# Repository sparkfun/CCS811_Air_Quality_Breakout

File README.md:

SparkFun CCS811 Air Quality Breakout
========================================

[*SparkFun CCS811 (SEN-14193)*](https://www.sparkfun.com/products/14193)

The CCS811 is an digital gas sensor solution which integrates a metal oxide (MOX) gas sensor to detect a wide range of Volatile Organic Compounds (VOCs) for indoor air quality monitoring.

This product is designed to provide an easy hardware and software interface to the CCS811 sensor.

Repository Contents
-------------------

* **/Documentation** - Data sheets, additional product information
* **/Hardware** - Eagle design files (.brd, .sch)
* **/Production** - Production panel files (.brd)
* **/Software** - Python scripts for CCS811

Documentation
--------------
* **[Library](https://github.com/sparkfun/SparkFun_CCS811_Arduino_Library)** - Arduino library for the CCS811.
* **[Hookup Guide](https://learn.sparkfun.com/tutorials/ccs811-air-quality-breakout-hookup-guide)** - Basic hookup guide for the CCS811.
* **[SparkFun Fritzing repo](https://github.com/sparkfun/Fritzing_Parts)** - Fritzing diagrams for SparkFun products.
* **[SparkFun 3D Model repo](https://github.com/sparkfun/3D_Models)** - 3D models of SparkFun products. 

Product Versions
----------------
* [SEN-14193](https://www.sparkfun.com/)- CCS811 Breakout board

Version History
---------------
* [V 1.0.0](https://github.com/sparkfun/CCS811_Air_Quality_Breakout/tree/V_1.0.0) -- Initial commit of Arduino compatible library.

License Information
-------------------

This product is _**open source**_! 

Please review the LICENSE.md file for license information. 

If you have any questions or concerns on licensing, please contact techsupport@sparkfun.com.

Distributed as-is; no warranty is given.

- Your friends at SparkFun.

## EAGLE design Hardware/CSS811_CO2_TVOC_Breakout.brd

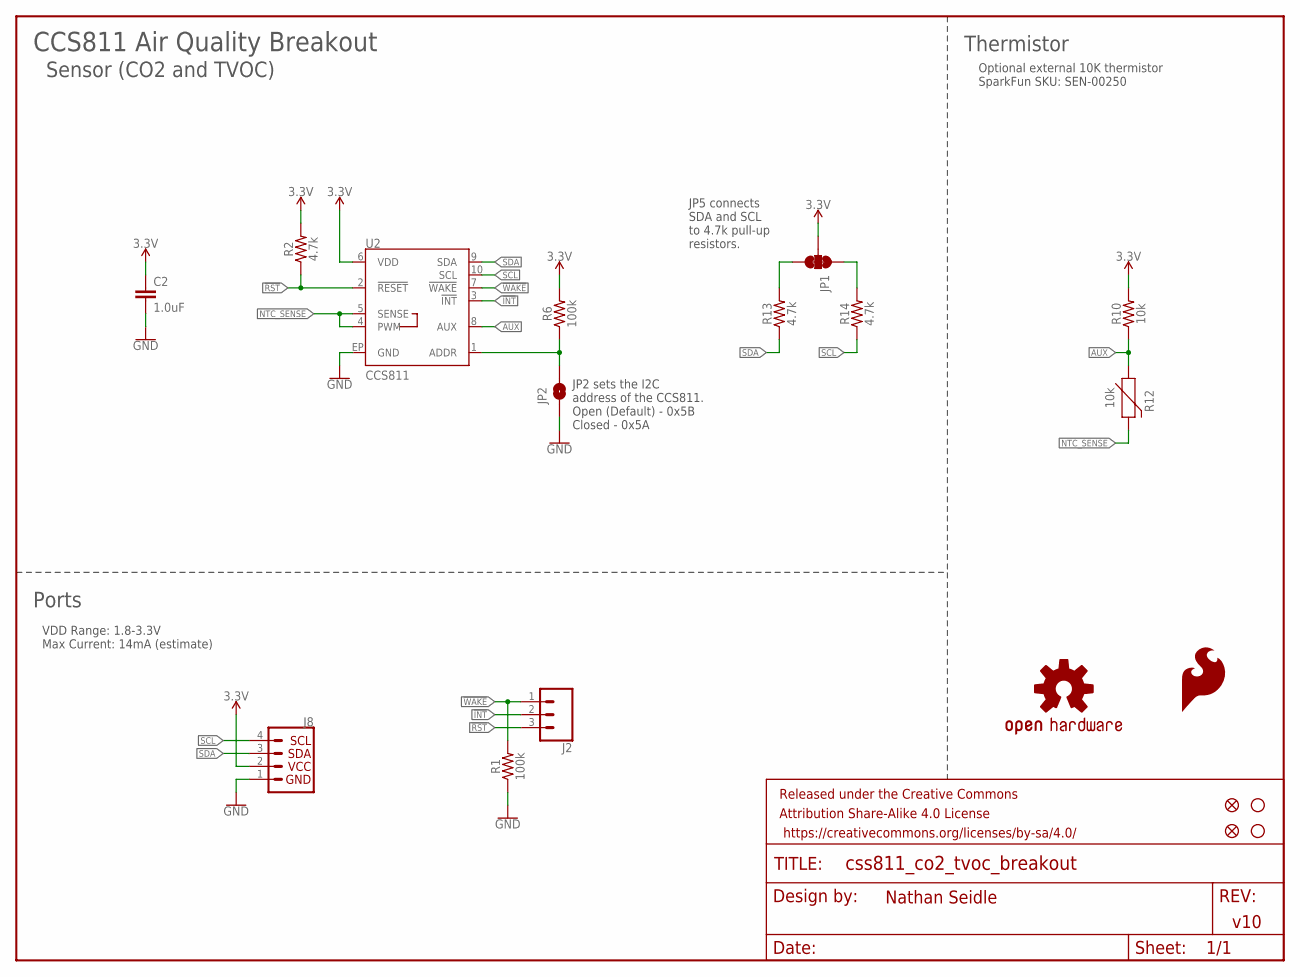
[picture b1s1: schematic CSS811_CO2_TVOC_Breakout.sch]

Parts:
C2: 1.0uF; 0603
FD1, FD2: FIDUCIAL1X2; FIDUCIAL-1X2
FRAME1: FRAME-LETTER; CREATIVE_COMMONS
H2, H4: STAND-OFF
J2: CONN_031X03_NO_SILK; 1X03_NO_SILK
J8: I2C_STANDARD_NO_SILK; 1X04_NO_SILK
JP1: JUMPER-SMT_3_2-NC_TRACE_SILK; SMT-JUMPER_3_2-NC_TRACE_SILK
JP2: JUMPER-SMT_2_NO_SILK; SMT-JUMPER_2_NO_SILK
LOGO1: SFE_LOGO_FLAME.2_INCH; SFE_LOGO_FLAME_.2
LOGO4: OSHW-LOGOS; OSHW-LOGO-S
R1, R6: 100k; 0603
R2, R13, R14: 4.7k; 0603
R10: 10k; 0603
R12: 10k; AXIAL-0.1
U2: CCS811; LGA10

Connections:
3.3V: C2.1, J8.2, JP1.2, R2.2, R6.2, R10.2, U2.6 (VDD)
!INT: J2.2, U2.3 (!INT!)
!RST: J2.3, R2.1, U2.2 (!RESET!)
!WAKE: J2.1, R1.2, U2.7 (!WAKE!)
AUX: R10.1, R12.P$1 (1), U2.8 (AUX)
CCS811_ADDR: JP2.2, R6.1, U2.1 (ADDR)
GND: C2.2, J8.1, JP2.1, R1.1, U2.EP (GND)
unnamed: JP1.3, R13.2
unnamed: JP1.1, R14.2
NTC_SENSE: R12.P$2 (2), U2.4 (PWM), U2.5 (SENSE)
SCL: J8.4, R14.1, U2.10 (SCL)
SDA: J8.3, R13.1, U2.9 (SDA)

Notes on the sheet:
VDD Range: 1.8-3.3V Max Current: 14mA (estimate)
CCS811 Air Quality Breakout
JP2 sets the I2C address of the CCS811. Open (Default) - 0x5B Closed - 0x5A
JP5 connects SDA and SCL to 4.7k pull-up resistors.
v10
Nathan Seidle
Optional external 10K thermistor SparkFun SKU: SEN-00250
Ports
Thermistor
Sensor (CO2 and TVOC)

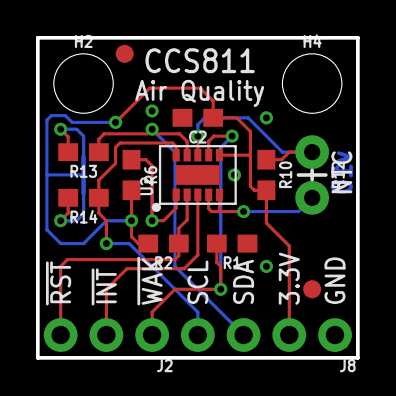
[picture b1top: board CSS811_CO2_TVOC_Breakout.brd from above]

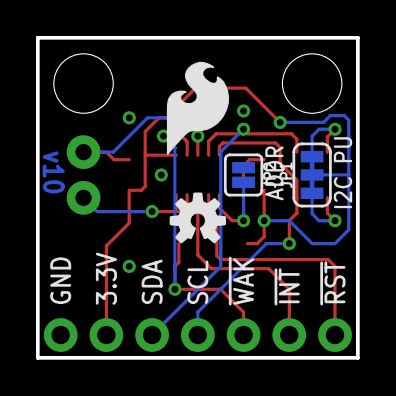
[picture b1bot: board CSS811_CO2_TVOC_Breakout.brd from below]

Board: 2 copper layers, 17.8 x 17.8 mm, 20 parts (4 on the bottom side), 12 nets.

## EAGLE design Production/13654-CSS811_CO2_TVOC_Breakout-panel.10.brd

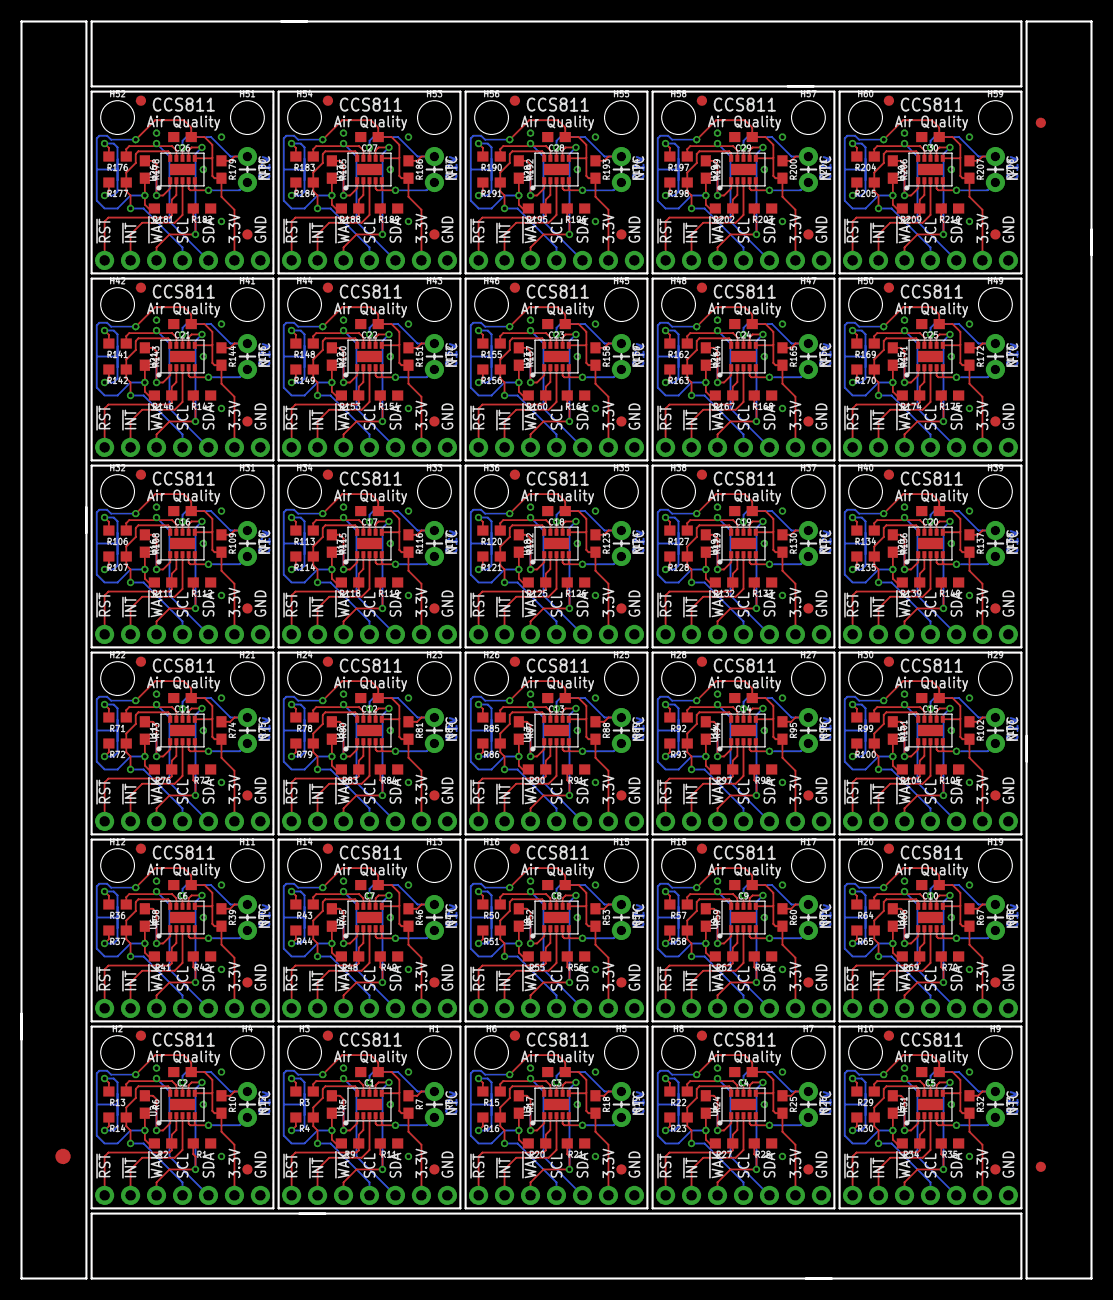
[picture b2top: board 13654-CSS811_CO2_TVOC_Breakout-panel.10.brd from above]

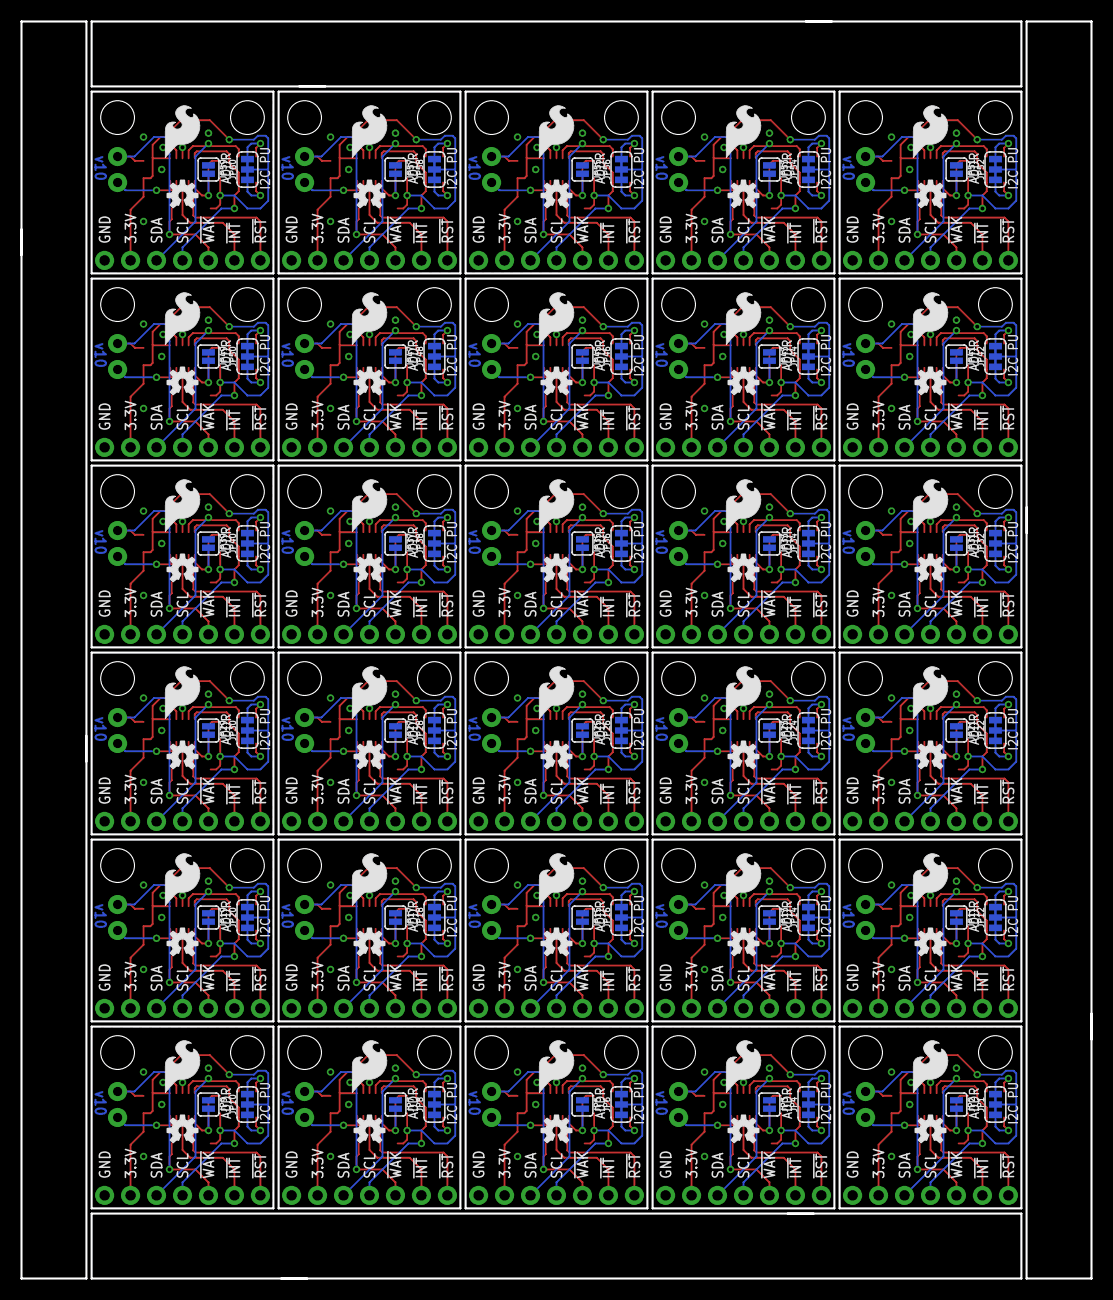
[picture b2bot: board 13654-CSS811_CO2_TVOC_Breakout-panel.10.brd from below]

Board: 2 copper layers, 104.6 x 122.9 mm, 573 parts (120 on the bottom side), 360 nets.

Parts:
C1, C2, C3, C4, C5, C6, C7, C8, C9, C10, C11, C12, C13, C14, C15, C16, C17, C18, C19, C20, C21, C22, C23, C24, C25, C26, C27, C28, C29, C30: 1.0uF; 0603
E$1: FIDUCIAL-1.5X3
E$7, E$8: FIDUCIAL-1X2
FD1, FD2, FD3, FD4, FD5, FD6, FD7, FD8, FD9, FD10, FD11, FD12, FD13, FD14, FD15, FD16, FD17, FD18, FD19, FD20, FD21, FD22, FD23, FD24, FD25, FD26, FD27, FD28, FD29, FD30, FD31, FD32, FD33, FD34, FD35, FD36, FD37, FD38, FD39, FD40, FD41, FD42, FD43, FD44, FD45, FD46, FD47, FD48, FD49, FD50, FD51, FD52, FD53, FD54, FD55, FD56, FD57, FD58, FD59, FD60: FIDUCIAL1X2; FIDUCIAL-1X2
H1, H2, H3, H4, H5, H6, H7, H8, H9, H10, H11, H12, H13, H14, H15, H16, H17, H18, H19, H20, H21, H22, H23, H24, H25, H26, H27, H28, H29, H30, H31, H32, H33, H34, H35, H36, H37, H38, H39, H40, H41, H42, H43, H44, H45, H46, H47, H48, H49, H50, H51, H52, H53, H54, H55, H56, H57, H58, H59, H60: STAND-OFF
J1, J4, J6, J8, J9, J11, J13, J15, J17, J19, J21, J23, J25, J27, J29, J31, J33, J35, J37, J39, J41, J43, J45, J47, J49, J51, J53, J55, J57, J59: 1X04_NO_SILK
J2, J3, J5, J7, J10, J12, J14, J16, J18, J20, J22, J24, J26, J28, J30, J32, J34, J36, J38, J40, J42, J44, J46, J48, J50, J52, J54, J56, J58, J60: 1X03_NO_SILK
JP1, JP4, JP6, JP8, JP10, JP12, JP14, JP16, JP18, JP20, JP22, JP24, JP26, JP28, JP30, JP32, JP34, JP36, JP38, JP40, JP42, JP44, JP46, JP48, JP50, JP52, JP54, JP56, JP58, JP60: SMT-JUMPER_3_2-NC_TRACE_SILK
JP2, JP3, JP5, JP7, JP9, JP11, JP13, JP15, JP17, JP19, JP21, JP23, JP25, JP27, JP29, JP31, JP33, JP35, JP37, JP39, JP41, JP43, JP45, JP47, JP49, JP51, JP53, JP55, JP57, JP59: SMT-JUMPER_2_NO_SILK
LOGO1, LOGO3, LOGO6, LOGO8, LOGO10, LOGO12, LOGO14, LOGO16, LOGO18, LOGO20, LOGO22, LOGO24, LOGO26, LOGO28, LOGO30, LOGO32, LOGO34, LOGO36, LOGO38, LOGO40, LOGO42, LOGO44, LOGO46, LOGO48, LOGO50, LOGO52, LOGO54, LOGO56, LOGO58, LOGO60: SFE_LOGO_FLAME.2_INCH; SFE_LOGO_FLAME_.2
LOGO2, LOGO4, LOGO5, LOGO7, LOGO9, LOGO11, LOGO13, LOGO15, LOGO17, LOGO19, LOGO21, LOGO23, LOGO25, LOGO27, LOGO29, LOGO31, LOGO33, LOGO35, LOGO37, LOGO39, LOGO41, LOGO43, LOGO45, LOGO47, LOGO49, LOGO51, LOGO53, LOGO55, LOGO57, LOGO59: OSHW-LOGOS; OSHW-LOGO-S
R1, R5, R6, R11, R17, R21, R24, R28, R31, R35, R38, R42, R45, R49, R52, R56, R59, R63, R66, R70, R73, R77, R80, R84, R87, R91, R94, R98, R101, R105, R108, R112, R115, R119, R122, R126, R129, R133, R136, R140, R143, R147, R150, R154, R157, R161, R164, R168, R171, R175, R178, R182, R185, R189, R192, R196, R199, R203, R206, R210: 100k; 0603
R2, R3, R4, R9, R13, R14, R15, R16, R20, R22, R23, R27, R29, R30, R34, R36, R37, R41, R43, R44, R48, R50, R51, R55, R57, R58, R62, R64, R65, R69, R71, R72, R76, R78, R79, R83, R85, R86, R90, R92, R93, R97, R99, R100, R104, R106, R107, R111, R113, R114, R118, R120, R121, R125, R127, R128, R132, R134, R135, R139, R141, R142, R146, R148, R149, R153, R155, R156, R160, R162, R163, R167, R169, R170, R174, R176, R177, R181, R183, R184, R188, R190, R191, R195, R197, R198, R202, R204, R205, R209: 4.7k; 0603
R7, R10, R18, R25, R32, R39, R46, R53, R60, R67, R74, R81, R88, R95, R102, R109, R116, R123, R130, R137, R144, R151, R158, R165, R172, R179, R186, R193, R200, R207: 10k; 0603
R8, R12, R19, R26, R33, R40, R47, R54, R61, R68, R75, R82, R89, R96, R103, R110, R117, R124, R131, R138, R145, R152, R159, R166, R173, R180, R187, R194, R201, R208: 10k; AXIAL-0.1
U1, U2, U3, U4, U5, U6, U7, U8, U9, U10, U11, U12, U13, U14, U15, U16, U17, U18, U19, U20, U21, U22, U23, U24, U25, U26, U27, U28, U29, U30: CCS811; LGA10

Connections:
3.3V: C2.1, J8.2, JP1.2, R2.2, R6.2, R10.2, U2.6
3.3V1: C1.1, J1.2, JP4.2, R5.2, R7.2, R9.2, U1.6
3.3V2: C3.1, J4.2, JP6.2, R17.2, R18.2, R20.2, U3.6
3.3V3: C4.1, J6.2, JP8.2, R24.2, R25.2, R27.2, U4.6
3.3V4: C5.1, J9.2, JP10.2, R31.2, R32.2, R34.2, U5.6
3.3V5: C6.1, J11.2, JP12.2, R38.2, R39.2, R41.2, U6.6
3.3V6: C7.1, J13.2, JP14.2, R45.2, R46.2, R48.2, U7.6
3.3V7: C8.1, J15.2, JP16.2, R52.2, R53.2, R55.2, U8.6
3.3V8: C9.1, J17.2, JP18.2, R59.2, R60.2, R62.2, U9.6
3.3V9: C10.1, J19.2, JP20.2, R66.2, R67.2, R69.2, U10.6
3.3V10: C11.1, J21.2, JP22.2, R73.2, R74.2, R76.2, U11.6
3.3V11: C12.1, J23.2, JP24.2, R80.2, R81.2, R83.2, U12.6
3.3V12: C13.1, J25.2, JP26.2, R87.2, R88.2, R90.2, U13.6
3.3V13: C14.1, J27.2, JP28.2, R94.2, R95.2, R97.2, U14.6
3.3V14: C15.1, J29.2, JP30.2, R101.2, R102.2, R104.2, U15.6
3.3V15: C16.1, J31.2, JP32.2, R108.2, R109.2, R111.2, U16.6
3.3V16: C17.1, J33.2, JP34.2, R115.2, R116.2, R118.2, U17.6
3.3V17: C18.1, J35.2, JP36.2, R122.2, R123.2, R125.2, U18.6
3.3V18: C19.1, J37.2, JP38.2, R129.2, R130.2, R132.2, U19.6
3.3V19: C20.1, J39.2, JP40.2, R136.2, R137.2, R139.2, U20.6
3.3V20: C21.1, J41.2, JP42.2, R143.2, R144.2, R146.2, U21.6
3.3V21: C22.1, J43.2, JP44.2, R150.2, R151.2, R153.2, U22.6
3.3V22: C23.1, J45.2, JP46.2, R157.2, R158.2, R160.2, U23.6
3.3V23: C24.1, J47.2, JP48.2, R164.2, R165.2, R167.2, U24.6
3.3V24: C25.1, J49.2, JP50.2, R171.2, R172.2, R174.2, U25.6
3.3V25: C26.1, J51.2, JP52.2, R178.2, R179.2, R181.2, U26.6
3.3V26: C27.1, J53.2, JP54.2, R185.2, R186.2, R188.2, U27.6
3.3V27: C28.1, J55.2, JP56.2, R192.2, R193.2, R195.2, U28.6
3.3V28: C29.1, J57.2, JP58.2, R199.2, R200.2, R202.2, U29.6
3.3V29: C30.1, J59.2, JP60.2, R206.2, R207.2, R209.2, U30.6
!INT: J2.2, U2.3
!INT1: J3.2, U1.3
!INT2: J5.2, U3.3
!INT3: J7.2, U4.3
!INT4: J10.2, U5.3
!INT5: J12.2, U6.3
!INT6: J14.2, U7.3
!INT7: J16.2, U8.3
!INT8: J18.2, U9.3
!INT9: J20.2, U10.3
!INT10: J22.2, U11.3
!INT11: J24.2, U12.3
!INT12: J26.2, U13.3
!INT13: J28.2, U14.3
!INT14: J30.2, U15.3
!INT15: J32.2, U16.3
!INT16: J34.2, U17.3
!INT17: J36.2, U18.3
!INT18: J38.2, U19.3
!INT19: J40.2, U20.3
!INT20: J42.2, U21.3
!INT21: J44.2, U22.3
!INT22: J46.2, U23.3
!INT23: J48.2, U24.3
!INT24: J50.2, U25.3
!INT25: J52.2, U26.3
!INT26: J54.2, U27.3
!INT27: J56.2, U28.3
!INT28: J58.2, U29.3
!INT29: J60.2, U30.3
!RST: J2.3, R2.1, U2.2
!RST1: J3.3, R9.1, U1.2
!RST2: J5.3, R20.1, U3.2
!RST3: J7.3, R27.1, U4.2
!RST4: J10.3, R34.1, U5.2
!RST5: J12.3, R41.1, U6.2
!RST6: J14.3, R48.1, U7.2
!RST7: J16.3, R55.1, U8.2
!RST8: J18.3, R62.1, U9.2
!RST9: J20.3, R69.1, U10.2
!RST10: J22.3, R76.1, U11.2
!RST11: J24.3, R83.1, U12.2
!RST12: J26.3, R90.1, U13.2
!RST13: J28.3, R97.1, U14.2
!RST14: J30.3, R104.1, U15.2
!RST15: J32.3, R111.1, U16.2
!RST16: J34.3, R118.1, U17.2
!RST17: J36.3, R125.1, U18.2
!RST18: J38.3, R132.1, U19.2
!RST19: J40.3, R139.1, U20.2
!RST20: J42.3, R146.1, U21.2
!RST21: J44.3, R153.1, U22.2
!RST22: J46.3, R160.1, U23.2
!RST23: J48.3, R167.1, U24.2
!RST24: J50.3, R174.1, U25.2
!RST25: J52.3, R181.1, U26.2
!RST26: J54.3, R188.1, U27.2
!RST27: J56.3, R195.1, U28.2
!RST28: J58.3, R202.1, U29.2
!RST29: J60.3, R209.1, U30.2
!WAKE: J2.1, R1.2, U2.7
!WAKE1: J3.1, R11.2, U1.7
!WAKE2: J5.1, R21.2, U3.7
!WAKE3: J7.1, R28.2, U4.7
!WAKE4: J10.1, R35.2, U5.7
!WAKE5: J12.1, R42.2, U6.7
!WAKE6: J14.1, R49.2, U7.7
!WAKE7: J16.1, R56.2, U8.7
!WAKE8: J18.1, R63.2, U9.7
!WAKE9: J20.1, R70.2, U10.7
!WAKE10: J22.1, R77.2, U11.7
!WAKE11: J24.1, R84.2, U12.7
!WAKE12: J26.1, R91.2, U13.7
!WAKE13: J28.1, R98.2, U14.7
!WAKE14: J30.1, R105.2, U15.7
!WAKE15: J32.1, R112.2, U16.7
!WAKE16: J34.1, R119.2, U17.7
!WAKE17: J36.1, R126.2, U18.7
!WAKE18: J38.1, R133.2, U19.7
!WAKE19: J40.1, R140.2, U20.7
!WAKE20: J42.1, R147.2, U21.7
!WAKE21: J44.1, R154.2, U22.7
!WAKE22: J46.1, R161.2, U23.7
!WAKE23: J48.1, R168.2, U24.7
!WAKE24: J50.1, R175.2, U25.7
!WAKE25: J52.1, R182.2, U26.7
!WAKE26: J54.1, R189.2, U27.7
!WAKE27: J56.1, R196.2, U28.7
!WAKE28: J58.1, R203.2, U29.7
!WAKE29: J60.1, R210.2, U30.7
AUX: R10.1, R12.P$1, U2.8
AUX1: R7.1, R8.P$1, U1.8
AUX2: R18.1, R19.P$1, U3.8
AUX3: R25.1, R26.P$1, U4.8
AUX4: R32.1, R33.P$1, U5.8
AUX5: R39.1, R40.P$1, U6.8
AUX6: R46.1, R47.P$1, U7.8
AUX7: R53.1, R54.P$1, U8.8
AUX8: R60.1, R61.P$1, U9.8
AUX9: R67.1, R68.P$1, U10.8
AUX10: R74.1, R75.P$1, U11.8
AUX11: R81.1, R82.P$1, U12.8
AUX12: R88.1, R89.P$1, U13.8
AUX13: R95.1, R96.P$1, U14.8
AUX14: R102.1, R103.P$1, U15.8
AUX15: R109.1, R110.P$1, U16.8
AUX16: R116.1, R117.P$1, U17.8
AUX17: R123.1, R124.P$1, U18.8
AUX18: R130.1, R131.P$1, U19.8
AUX19: R137.1, R138.P$1, U20.8
AUX20: R144.1, R145.P$1, U21.8
AUX21: R151.1, R152.P$1, U22.8
AUX22: R158.1, R159.P$1, U23.8
AUX23: R165.1, R166.P$1, U24.8
AUX24: R172.1, R173.P$1, U25.8
AUX25: R179.1, R180.P$1, U26.8
AUX26: R186.1, R187.P$1, U27.8
AUX27: R193.1, R194.P$1, U28.8
AUX28: R200.1, R201.P$1, U29.8
AUX29: R207.1, R208.P$1, U30.8
CCS811_ADDR: JP2.2, R6.1, U2.1
CCS811_ADDR1: JP3.2, R5.1, U1.1
CCS811_ADDR2: JP5.2, R17.1, U3.1
CCS811_ADDR3: JP7.2, R24.1, U4.1
CCS811_ADDR4: JP9.2, R31.1, U5.1
CCS811_ADDR5: JP11.2, R38.1, U6.1
CCS811_ADDR6: JP13.2, R45.1, U7.1
CCS811_ADDR7: JP15.2, R52.1, U8.1
CCS811_ADDR8: JP17.2, R59.1, U9.1
CCS811_ADDR9: JP19.2, R66.1, U10.1
CCS811_ADDR10: JP21.2, R73.1, U11.1
CCS811_ADDR11: JP23.2, R80.1, U12.1
CCS811_ADDR12: JP25.2, R87.1, U13.1
CCS811_ADDR13: JP27.2, R94.1, U14.1
CCS811_ADDR14: JP29.2, R101.1, U15.1
CCS811_ADDR15: JP31.2, R108.1, U16.1
CCS811_ADDR16: JP33.2, R115.1, U17.1
CCS811_ADDR17: JP35.2, R122.1, U18.1
CCS811_ADDR18: JP37.2, R129.1, U19.1
CCS811_ADDR19: JP39.2, R136.1, U20.1
CCS811_ADDR20: JP41.2, R143.1, U21.1
CCS811_ADDR21: JP43.2, R150.1, U22.1
CCS811_ADDR22: JP45.2, R157.1, U23.1
CCS811_ADDR23: JP47.2, R164.1, U24.1
CCS811_ADDR24: JP49.2, R171.1, U25.1
CCS811_ADDR25: JP51.2, R178.1, U26.1
CCS811_ADDR26: JP53.2, R185.1, U27.1
CCS811_ADDR27: JP55.2, R192.1, U28.1
CCS811_ADDR28: JP57.2, R199.1, U29.1
CCS811_ADDR29: JP59.2, R206.1, U30.1
GND: C2.2, J8.1, JP2.1, R1.1, U2.EP
GND1: C1.2, J1.1, JP3.1, R11.1, U1.EP
GND2: C3.2, J4.1, JP5.1, R21.1, U3.EP
GND3: C4.2, J6.1, JP7.1, R28.1, U4.EP
GND4: C5.2, J9.1, JP9.1, R35.1, U5.EP
GND5: C6.2, J11.1, JP11.1, R42.1, U6.EP
GND6: C7.2, J13.1, JP13.1, R49.1, U7.EP
GND7: C8.2, J15.1, JP15.1, R56.1, U8.EP
GND8: C9.2, J17.1, JP17.1, R63.1, U9.EP
GND9: C10.2, J19.1, JP19.1, R70.1, U10.EP
GND10: C11.2, J21.1, JP21.1, R77.1, U11.EP
GND11: C12.2, J23.1, JP23.1, R84.1, U12.EP
GND12: C13.2, J25.1, JP25.1, R91.1, U13.EP
GND13: C14.2, J27.1, JP27.1, R98.1, U14.EP
GND14: C15.2, J29.1, JP29.1, R105.1, U15.EP
GND15: C16.2, J31.1, JP31.1, R112.1, U16.EP
GND16: C17.2, J33.1, JP33.1, R119.1, U17.EP
GND17: C18.2, J35.1, JP35.1, R126.1, U18.EP
GND18: C19.2, J37.1, JP37.1, R133.1, U19.EP
GND19: C20.2, J39.1, JP39.1, R140.1, U20.EP
GND20: C21.2, J41.1, JP41.1, R147.1, U21.EP
GND21: C22.2, J43.1, JP43.1, R154.1, U22.EP
GND22: C23.2, J45.1, JP45.1, R161.1, U23.EP
GND23: C24.2, J47.1, JP47.1, R168.1, U24.EP
GND24: C25.2, J49.1, JP49.1, R175.1, U25.EP
GND25: C26.2, J51.1, JP51.1, R182.1, U26.EP
GND26: C27.2, J53.1, JP53.1, R189.1, U27.EP
GND27: C28.2, J55.1, JP55.1, R196.1, U28.EP
GND28: C29.2, J57.1, JP57.1, R203.1, U29.EP
GND29: C30.2, J59.1, JP59.1, R210.1, U30.EP
unnamed: JP4.3, R3.2
unnamed: JP4.1, R4.2
unnamed: JP6.3, R15.2
unnamed: JP1.3, R13.2
unnamed: JP1.1, R14.2
unnamed: JP6.1, R16.2
unnamed: JP8.3, R22.2
unnamed: JP8.1, R23.2
unnamed: JP10.3, R29.2
unnamed: JP10.1, R30.2
unnamed: JP12.3, R36.2
unnamed: JP12.1, R37.2
unnamed: JP14.3, R43.2
unnamed: JP14.1, R44.2
unnamed: JP16.3, R50.2
unnamed: JP16.1, R51.2
unnamed: JP18.3, R57.2
unnamed: JP18.1, R58.2
unnamed: JP20.3, R64.2
unnamed: JP20.1, R65.2
unnamed: JP22.3, R71.2
unnamed: JP22.1, R72.2
unnamed: JP24.3, R78.2
unnamed: JP24.1, R79.2
unnamed: JP26.3, R85.2
unnamed: JP26.1, R86.2
unnamed: JP28.3, R92.2
unnamed: JP28.1, R93.2
unnamed: JP30.3, R99.2
unnamed: JP30.1, R100.2
unnamed: JP32.3, R106.2
unnamed: JP32.1, R107.2
unnamed: JP34.3, R113.2
unnamed: JP34.1, R114.2
unnamed: JP36.3, R120.2
unnamed: JP36.1, R121.2
unnamed: JP38.3, R127.2
unnamed: JP38.1, R128.2
unnamed: JP40.3, R134.2
unnamed: JP40.1, R135.2
unnamed: JP42.3, R141.2
unnamed: JP42.1, R142.2
unnamed: JP44.3, R148.2
unnamed: JP44.1, R149.2
unnamed: JP46.3, R155.2
unnamed: JP46.1, R156.2
unnamed: JP48.3, R162.2
unnamed: JP48.1, R163.2
unnamed: JP50.3, R169.2
unnamed: JP50.1, R170.2
unnamed: JP52.3, R176.2
unnamed: JP52.1, R177.2
unnamed: JP54.3, R183.2
unnamed: JP54.1, R184.2
unnamed: JP56.3, R190.2
unnamed: JP56.1, R191.2
unnamed: JP58.3, R197.2
unnamed: JP58.1, R198.2
unnamed: JP60.3, R204.2
unnamed: JP60.1, R205.2
NTC_SENSE: R12.P$2, U2.4, U2.5
NTC_SENSE1: R8.P$2, U1.4, U1.5
NTC_SENSE2: R19.P$2, U3.4, U3.5
NTC_SENSE3: R26.P$2, U4.4, U4.5
NTC_SENSE4: R33.P$2, U5.4, U5.5
NTC_SENSE5: R40.P$2, U6.4, U6.5
NTC_SENSE6: R47.P$2, U7.4, U7.5
NTC_SENSE7: R54.P$2, U8.4, U8.5
NTC_SENSE8: R61.P$2, U9.4, U9.5
NTC_SENSE9: R68.P$2, U10.4, U10.5
NTC_SENSE10: R75.P$2, U11.4, U11.5
NTC_SENSE11: R82.P$2, U12.4, U12.5
NTC_SENSE12: R89.P$2, U13.4, U13.5
NTC_SENSE13: R96.P$2, U14.4, U14.5
NTC_SENSE14: R103.P$2, U15.4, U15.5
NTC_SENSE15: R110.P$2, U16.4, U16.5
NTC_SENSE16: R117.P$2, U17.4, U17.5
NTC_SENSE17: R124.P$2, U18.4, U18.5
NTC_SENSE18: R131.P$2, U19.4, U19.5
NTC_SENSE19: R138.P$2, U20.4, U20.5
NTC_SENSE20: R145.P$2, U21.4, U21.5
NTC_SENSE21: R152.P$2, U22.4, U22.5
NTC_SENSE22: R159.P$2, U23.4, U23.5
NTC_SENSE23: R166.P$2, U24.4, U24.5
NTC_SENSE24: R173.P$2, U25.4, U25.5
NTC_SENSE25: R180.P$2, U26.4, U26.5
NTC_SENSE26: R187.P$2, U27.4, U27.5
NTC_SENSE27: R194.P$2, U28.4, U28.5
NTC_SENSE28: R201.P$2, U29.4, U29.5
NTC_SENSE29: R208.P$2, U30.4, U30.5
SCL: J8.4, R14.1, U2.10
SCL1: J1.4, R4.1, U1.10
SCL2: J4.4, R16.1, U3.10
SCL3: J6.4, R23.1, U4.10
SCL4: J9.4, R30.1, U5.10
SCL5: J11.4, R37.1, U6.10
SCL6: J13.4, R44.1, U7.10
SCL7: J15.4, R51.1, U8.10
SCL8: J17.4, R58.1, U9.10
SCL9: J19.4, R65.1, U10.10
SCL10: J21.4, R72.1, U11.10
SCL11: J23.4, R79.1, U12.10
SCL12: J25.4, R86.1, U13.10
SCL13: J27.4, R93.1, U14.10
SCL14: J29.4, R100.1, U15.10
SCL15: J31.4, R107.1, U16.10
SCL16: J33.4, R114.1, U17.10
SCL17: J35.4, R121.1, U18.10
SCL18: J37.4, R128.1, U19.10
SCL19: J39.4, R135.1, U20.10
SCL20: J41.4, R142.1, U21.10
SCL21: J43.4, R149.1, U22.10
SCL22: J45.4, R156.1, U23.10
SCL23: J47.4, R163.1, U24.10
SCL24: J49.4, R170.1, U25.10
SCL25: J51.4, R177.1, U26.10
SCL26: J53.4, R184.1, U27.10
SCL27: J55.4, R191.1, U28.10
SCL28: J57.4, R198.1, U29.10
SCL29: J59.4, R205.1, U30.10
SDA: J8.3, R13.1, U2.9
SDA1: J1.3, R3.1, U1.9
SDA2: J4.3, R15.1, U3.9
SDA3: J6.3, R22.1, U4.9
SDA4: J9.3, R29.1, U5.9
SDA5: J11.3, R36.1, U6.9
SDA6: J13.3, R43.1, U7.9
SDA7: J15.3, R50.1, U8.9
SDA8: J17.3, R57.1, U9.9
SDA9: J19.3, R64.1, U10.9
SDA10: J21.3, R71.1, U11.9
SDA11: J23.3, R78.1, U12.9
SDA12: J25.3, R85.1, U13.9
SDA13: J27.3, R92.1, U14.9
SDA14: J29.3, R99.1, U15.9
SDA15: J31.3, R106.1, U16.9
SDA16: J33.3, R113.1, U17.9
SDA17: J35.3, R120.1, U18.9
SDA18: J37.3, R127.1, U19.9
SDA19: J39.3, R134.1, U20.9
SDA20: J41.3, R141.1, U21.9
SDA21: J43.3, R148.1, U22.9
SDA22: J45.3, R155.1, U23.9
SDA23: J47.3, R162.1, U24.9
SDA24: J49.3, R169.1, U25.9
SDA25: J51.3, R176.1, U26.9
SDA26: J53.3, R183.1, U27.9
SDA27: J55.3, R190.1, U28.9
SDA28: J57.3, R197.1, U29.9
SDA29: J59.3, R204.1, U30.9

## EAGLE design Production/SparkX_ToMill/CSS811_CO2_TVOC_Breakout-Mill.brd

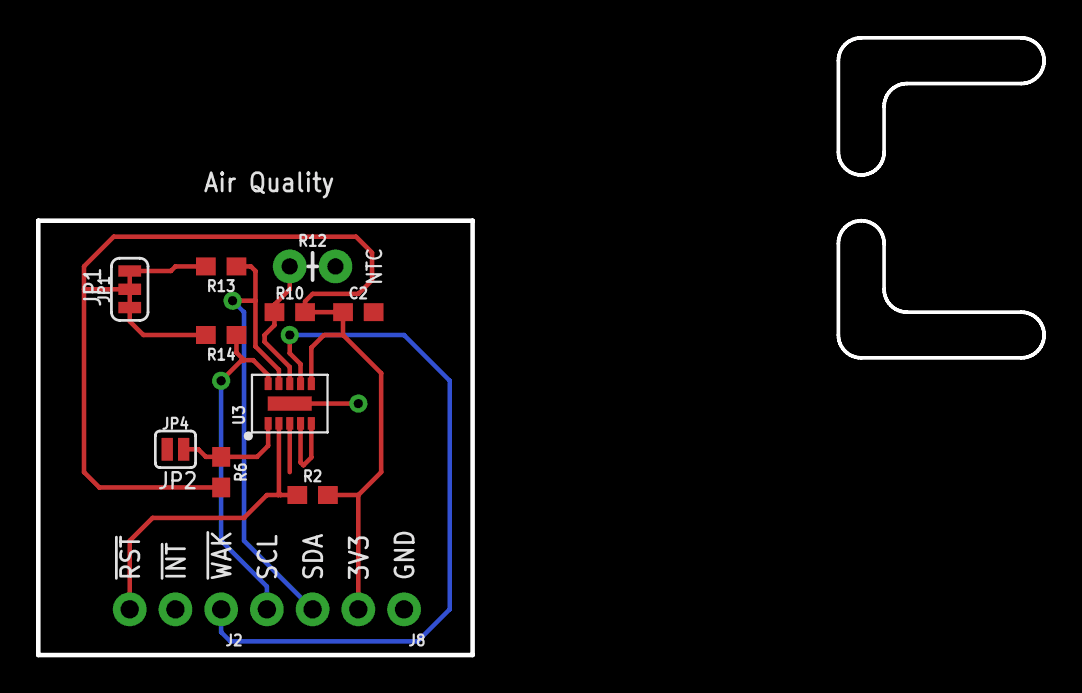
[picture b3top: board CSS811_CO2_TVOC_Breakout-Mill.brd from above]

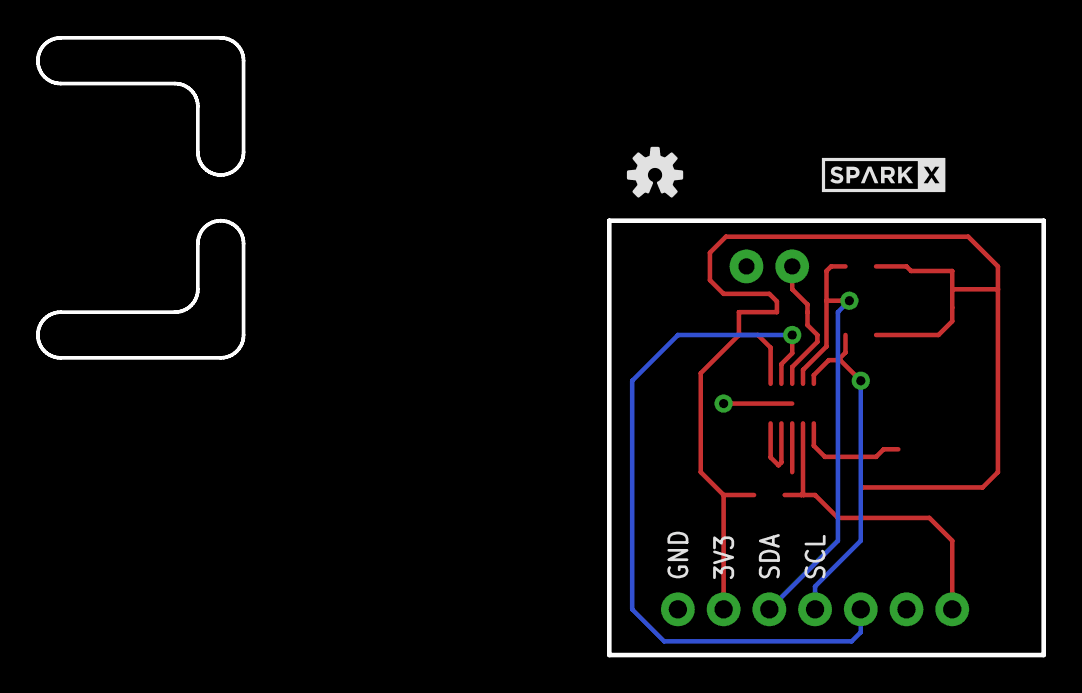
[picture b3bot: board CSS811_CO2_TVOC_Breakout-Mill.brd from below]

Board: 2 copper layers, 24.1 x 24.1 mm, 15 parts (2 on the bottom side), 12 nets.

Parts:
C2: 1.0uF; 0603
FRAME1: FRAME-LETTER; CREATIVE_COMMONS
J2: 1X03_NO_SILK
J8: 1X04_NO_SILK
JP1: SMT-JUMPER_3_2-NC_TRACE_SILK
JP4: SMT-JUMPER_2_NO_SILK
LOGO4: OSHW-LOGOS; OSHW-LOGO-S
R2, R13, R14: 4.7k; 0603
R6: 100k; 0603
R10: 10k; 0603
R12: DNP; AXIAL-0.1
U3: CCS811SKINNY; LGA10-MILLABLE
U$1: SPARKX-LOGO3; SPARKX-SMALL

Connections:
3.3V: C2.1, J8.2, JP1.2, R2.2, R6.2, R10.2, U3.6
!INT: J2.2, U3.3
!RST: J2.3, R2.1, U3.2
!WAKE: J2.1, U3.7
AUX: R10.1, R12.P$1, U3.8
CCS811_ADDR: JP4.2, R6.1, U3.1
GND: C2.2, J8.1, JP4.1, U3.EP
unnamed: JP1.3, R13.2
unnamed: JP1.1, R14.2
NTC_SENSE: R12.P$2, U3.4, U3.5
SCL: J8.4, R14.1, U3.10
SDA: J8.3, R13.1, U3.9

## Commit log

2017-02-05 :confetti_ball: Added .gitattributes & .gitignore files
2017-02-08 Adding panel and removing extraneous files.
2017-02-08 Adding panel
2017-02-08 Removing eagle backup files
2017-02-08 Reviewed and fixed Panel
2017-02-09 Rename datasheets
2017-02-09 Syncing
2017-02-09 Expanding examples. Adding docs.
2017-02-09 Fixed Gerber .zip file
2017-02-13 Removing extra layers on layout
2017-02-15 Added tight panel for ALLPCB
2017-02-15 Removing WAKE pin control to make examples simplier
2017-03-03 Restructed github to match standards
2017-03-03 Added temp library of new parts, added proper gitignore/gitattributes, switched sparkfun logo in for sparkx logo, cleaned up schematic, changed version number to v10
2017-03-06 Updated to take care of checklist and review items
2017-03-07 panel
2017-04-12 Added photo and fixed readme links
2017-04-27 Squashed library in
2017-04-27 Squashed 'Libraries/Arduino/' content from commit edd7744
    git-subtree-dir: Libraries/Arduino
    git-subtree-split: edd774432433c4d31eca30ce538e26dbf3343691
2017-06-08 ccs811 python example.
2017-06-08 Remove write to file option.
2019-01-23 Removing library and firmware from repo. See SparkFun CCS811 Arduino Library for the latest.
    Library: https://github.com/sparkfun/SparkFun_CCS811_Arduino_Library
2019-05-31 Add Updated CCS811 Datasheet

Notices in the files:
parts and their libraries:
SparkFun-Aesthetics: Licensing: Creative Commons ShareAlike 4.0 International - https://creativecommons.org/licenses/by-sa/4.0
SparkFun-Aesthetics: Released under the Creative Commons Attribution Share-Alike 4.0 License
SparkFun-Aesthetics: https://creativecommons.org/licenses/by-sa/4.0
